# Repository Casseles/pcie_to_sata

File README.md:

# 4-Layer PCIe-to-SATA Adapter (Marvell 88SE9215).

*3D rendering top side (KiCad Raytracing)*

---

## 1. Project Overview
A compact 4-layer PCIe Gen2 x1 to 4-Port SATA 6 Gbps expansion card designed around the **Marvell 88SE9215** controller. 
This project serves as a first step into a homemade NAS server (to simply store data like pictures or videos). 
The goal was to make it from old hardware like a laptop, this card would help to add storage from HDD or SDD from the PCIe port.
I designed everything so it can be made with **JLCPCB SMT Assembly** but the price is too expensive for now to take it into manufacturing.

---

## 2. Key Specifications & System Architecture

| Feature | Specification |
| :--- | :--- |
| **Host Interface** | PCIe Gen2 x1 (5.0 Gbps per lane, Gold Finger PCB Edge Connector) |
| **SATA Controller** | Marvell 88SE9215 (76-pin QFN) |
| **SATA Ports** | 4x Standard 7-pin SATA 6 Gbps connectors |
| **Clocking** | 25.000 MHz Passive Crystal Resonator (SMD 3225 4-Pin, $C_L = 12\text{ pF}$) |
| **Power Supply** | PCIe +3.3V bus power to dual step-down buck regulators ($1.8\text{ V}$ & $1.0\text{ V}$) |
| **PCB Form Factor** | 4-Layer Stack-up, ENIG finish, Chamfered PCIe Edge |

### Block Diagram
```text
  ┌─────────────────┐       ┌───────────────────────┐       ┌──────────────┐
  │  PCIe Gen2 x1   │ ────> │   Marvell 88SE9215    │ ────> │  4x SATA III │
  │ Edge Connector  │       │       (QFN-76)        │       │  Connectors  │
  └─────────────────┘       └───────────────────────┘       └──────────────┘
           │                            ▲
           │                            │ 25 MHz
         +3.3V                  ┌───────────────┐
           ▼                    │ 25MHz Crystal │
   ┌───────────────┐            └───────────────┘
   │ DC-DC Bucks   │
   │ 1.8V & 1.0V   │
   └───────────────┘
```

## 3. Hardware Design & Signal Integrity

### Stack-up 

Designed for a 4-layer PCB stack-up :
- Layer 1 : High-speed differential pairs (PCIe & SATA) + buck regulator's components.
- Layer 2 : Ground plane.
- Layer 3 : Power planes (+3V3 / +1V8 / +1V0).
- Layer 4 : Decoupling capacitors, simple routing. 

### Power Distribution Network

- Dual Buck converter (MP2122) supplying power for core (+1V0) and I/O (+1V8).  
A switching regulator has been used and not an LDO because, to transform a +3V3 into a +1V0, and LDO would dissipate all additionnal voltage into heat, which could be dangerous.
- Low ESR ceramic decoupling capacitors placed on bottom layer to minimize loop inductance. 
To calculate inductances and resistances around the Buck converter, I followed the MP2122 datasheet.  

### Differential pair

To calculate width of the traces inside a differential pair, I used Saturn PCB Toolkit.  
Based on FR4 TG135 caracteristics (JLCPCB basic) and aiming for a 100 Ohms impedance for both SATA and PCIe differential pairs,  
I found a spacing between traces of 0,13mm and a width of 0,09mm.  
There are 3 differential pairs on PCIe : PRX, PTX and CLK.
For the first two, as the pins on the chip were inverted compared to the PCIe port, I switched them.  
The PCIe 2.0 specifications indicate a lane polarity that permits this kind of switch.  

## 4. Design for Manufacturing

- Fiducials placed on edge rails to ensure optical alignment as well as pick & place (SMT components).
- PCIe Edge connector designed with ENIG surface finish for high insertion durability.
- Components matched to JLCPCB SMT library.

## 5. Repository Structure

.  
├── docs/  
│  ├── schematic.pdf  
│  ├── pcb_layout.pdf  
│  └── images/  
├── hardware/  
└── manufacturing/  
   ├── gerbers/   
   ├── bom/  
   └── cpl/  

## 6. Verification & DRC status

- Schematic : ERC clean (0 errors)
- PCB Layout : DRC clean (0 errors)

## 7. Future improvements

The first step would be to manufacture this pcb and test it's accuracy.  
For a second version, it would be interesting to add power to SATA connectors as this version only deals with data and an additionnal power input is needed for all hard drivers.  
It would be wise to also rethink the architecture around the connectors so that they can be pluged directly to the board without an additionnal cable.

## 8. Licence

Distributed under the MIT License. See LICENSE for more information.

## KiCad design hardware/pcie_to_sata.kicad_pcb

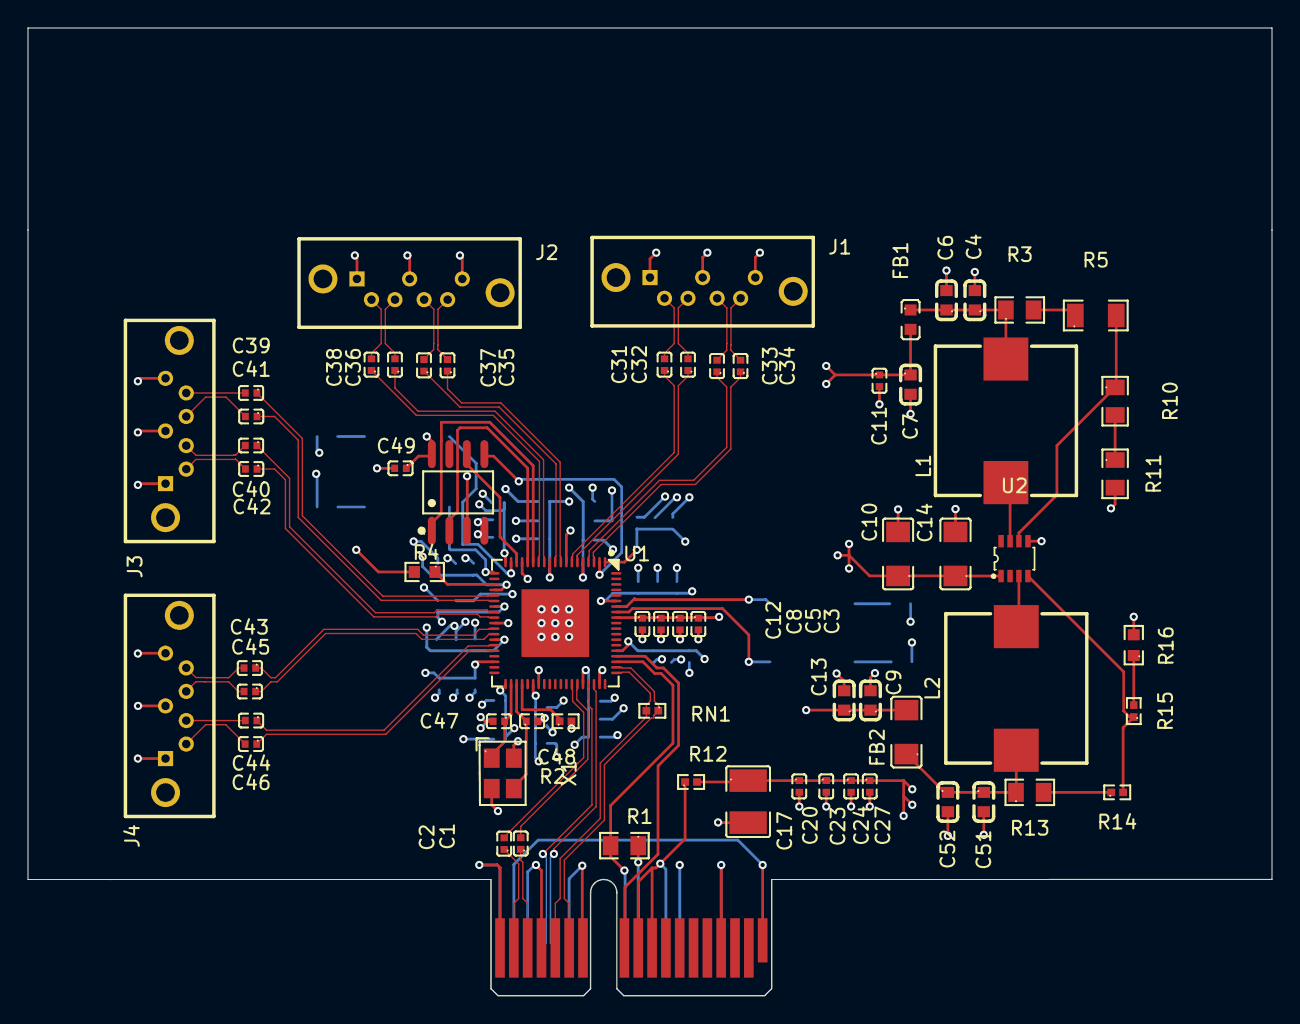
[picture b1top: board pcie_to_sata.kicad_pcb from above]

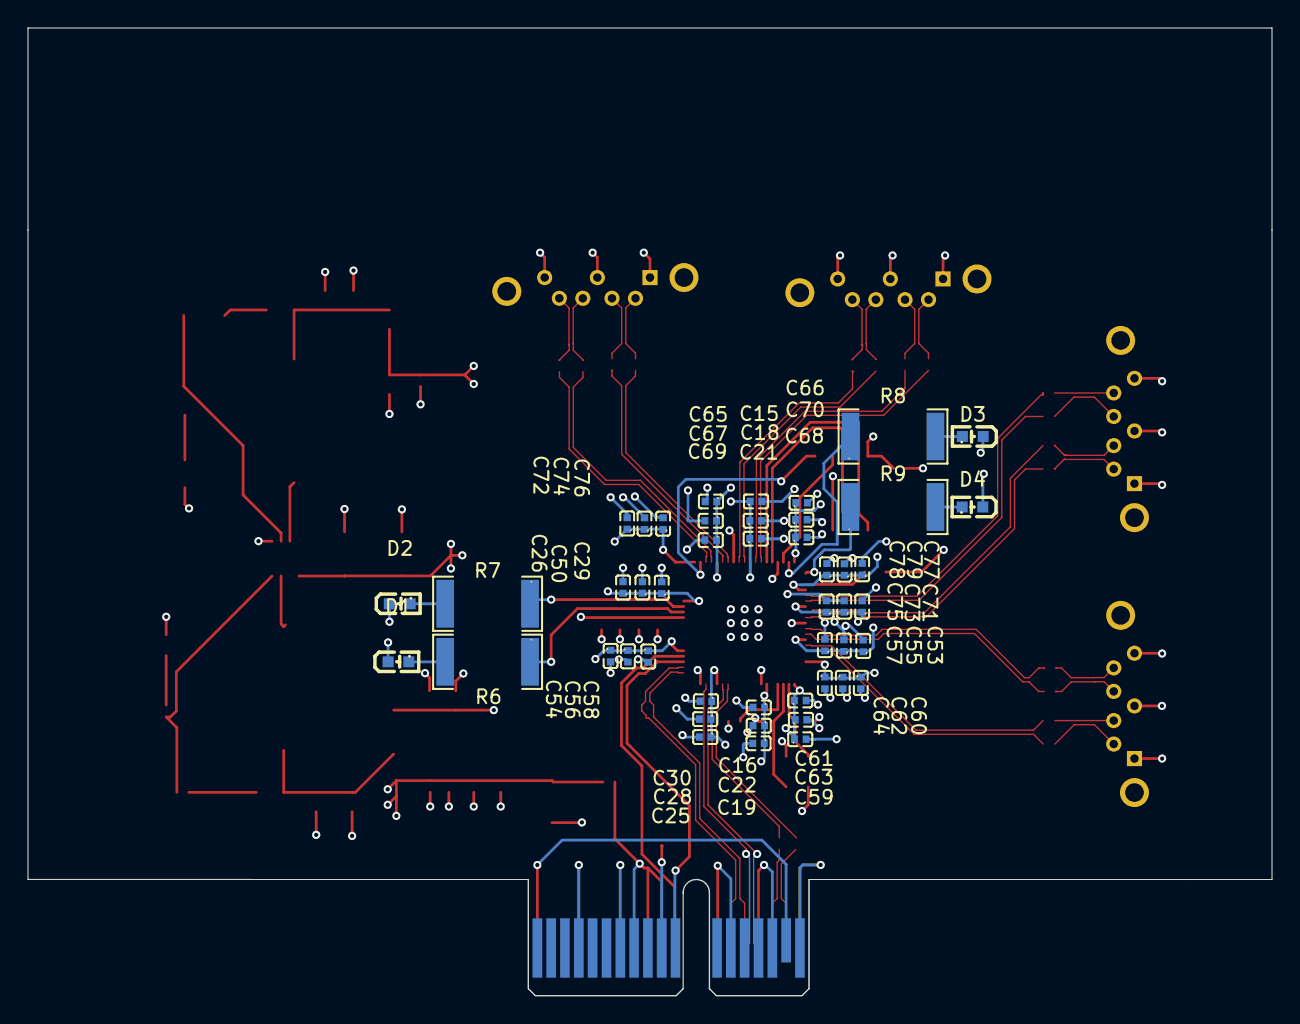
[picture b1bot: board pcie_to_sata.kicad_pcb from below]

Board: 4 copper layers, 90.0 x 70.0 mm, 113 parts (48 on the bottom side), 75 nets.

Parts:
C1, C2, C3, C5, C8, C11, C12, C15, C16, C20, C23, C24, C25, C26, C27, C49, C53, C54, C59, C60, C65, C66, C71, C72, C77: .1u; C0402
C4, C6, C51, C52: 10u; C0603
C7, C9: 2.2u; C0603
C10, C14: 22u; C1206
C13: 1u; C0603
C17: 100u; C1210
C18, C19, C22, C28, C29, C31, C32, C33, C34, C35, C36, C37, C38, C39, C40, C41, C42, C43, C44, C45, C46, C50, C55, C56, C58, C61, C62, C64, C67, C68, C70, C73, C74, C76, C78, C79: .01u; C0402
C21, C30, C57, C63, C69, C75: 1000p; C0402
C47, C48: 18p; C0402
D1, D2, D3, D4: LED; LED-SMD_L1.6-W0.8-R-RD
FB1: FerriteBead; L0603
FB2: FerriteBead; L1206
J1, J2, J3, J4: CONN-TH_SATA-501-M07S1BY-A
J5: Bus_PCI_Express_x1; BUS_PCIexpress_x1
L1, L2: 1.5u; IND-SMD_L10.8-W10.2_IHLP4040DZER1R8M11
R1: 4,7k; R0805
R2: 6.04k; R0402
R3: 750k; R0805
R4, R16: 10k; R0603
R5: 56k; R1206
R6, R7, R8, R9: 100; R2512
R10: 390k; R0805
R11: 22k; R0805
R12: 0; R0402
R13: 560k; R0805
R14: 39k; R0402
R15: 910k; R0402
RN1: 100; R0402
U1: QFN-76_L9.0-W9.0-P0.40-TL-EP4.9
U2: TSOT-23-8_L2.9-W1.6-P0.65-LS2.8-BL
U3: FM25Q08B-SO-T-G; SOP-8_L5.0-W4.0-P1.27-LS6.0-BL
X1: X322525MSB4SI; CRYSTAL-SMD_4P-L3.2-W2.5-BL-2

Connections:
+1V0: C9.1, C13.1, C16.1, C19.1, C22.1, C26.1, C29.1, C50.1, C54.1, C56.1, C58.1, C60.1, C62.1, C64.1, C66.1, C68.1, C70.1, C72.1, C74.1, C76.1, C77.1, C78.1, C79.1, FB2.2, U1.1 (VDD), U1.19 (VDD), U1.23 (VDD), U1.36 (VDD), U1.44 (VDD), U1.62 (VDD), U1.71 (VDD)
+1V0_unf: C51.1, C52.1, FB2.1, L2.2, R13.1
+1V8: C7.1, C11.1, C15.1, C18.1, C21.1, C25.1, C28.1, C30.1, C53.1, C55.1, C57.1, C59.1, C61.1, C63.1, C65.1, C67.1, C69.1, C71.1, C73.1, C75.1, FB1.2, U1.5 (VAA2_3), U1.11 (VAA2_2), U1.26 (VAA2_1), U1.32 (VAA2_0), U1.39 (VAA_1), U1.53 (AVDD0)
+1V8_unf: C4.1, C6.1, FB1.1, L1.1, R3.1
+3V3: C3.1, C5.1, C8.1, C10.1, C12.1, C14.1, C17.1, C20.1, C23.1, C24.1, C27.1, C49.1, D1.2 (A), D2.2 (A), D3.2 (A), D4.2 (A), R12.2, U1.16 (VDDIO), U1.68 (VDDIO), U2.1 (IN), U3.3 (WP#(DQ2)), U3.8 (VCC)
+3V3_unf: J5.A9 (+3.3V), J5.A10 (+3.3V), J5.B8 (+3.3V), R12.1
/pcie_to_sata/GPIO1: R6.1, U1.69 (GPIO1)
/pcie_to_sata/GPIO2: R7.1, U1.70 (GPIO2)
/pcie_to_sata/GPIO3: R8.1, U1.18 (GPIO3)
/pcie_to_sata/GPIO4: R9.1, U1.20 (GPIO4)
/pcie_to_sata/HSIN: C2.1, J5.A17 (PERn0)
/pcie_to_sata/HSIP: C1.1, J5.A16 (PERp0)
/pcie_to_sata/PCIE_AUX3: J5.B10 (3.3Vaux), R1.1
/pcie_to_sata/PCLKN: J5.A14 (REFCLK-), RN1.2, U1.58 (CLKP)
/pcie_to_sata/PCLKP: J5.A13 (REFCLK+), RN1.1, U1.59 (CLKN)
/pcie_to_sata/PERST_N: J5.A11 (~PERST), U1.61 (PERST_N)
/pcie_to_sata/PRX_0N: J5.B15 (PETn0), U1.54 (PRXN0)
/pcie_to_sata/PRX_0P: J5.B14 (PETp0), U1.55 (PRXP0)
/pcie_to_sata/PTX_0N: C1.2, U1.52 (PTXP0)
/pcie_to_sata/PTX_0P: C2.2, U1.51 (PTXN0)
/pcie_to_sata/SPI_CLK: U1.17 (SPI_CLK), U3.6 (CLK)
/pcie_to_sata/SPI_CS: U1.14 (SPI_CS), U3.1 (~CS)
/pcie_to_sata/SPI_DI: U1.15 (SPI_DI), U3.2 (DO(DQ1))
/pcie_to_sata/SPI_DO: U1.2 (SPI_DO), U3.5 (DI(DQ0))
/pcie_to_sata/S_RXN0: C33.1, U1.4 (RXN_3)
/pcie_to_sata/S_RXN0_: C33.2, J1.5
/pcie_to_sata/S_RXN1: C37.1, U1.10 (RXN_2)
/pcie_to_sata/S_RXN1_: C37.2, J2.5
/pcie_to_sata/S_RXN2: C41.1, U1.25 (RXN_1)
/pcie_to_sata/S_RXN2_: C41.2, J3.5
/pcie_to_sata/S_RXN3: C45.1, U1.31 (RXN_0)
/pcie_to_sata/S_RXN3_: C45.2, J4.5
/pcie_to_sata/S_RXP0: C34.1, U1.3 (RXP_3)
/pcie_to_sata/S_RXP0_: C34.2, J1.6
/pcie_to_sata/S_RXP1: C35.1, U1.9 (RXP_2)
/pcie_to_sata/S_RXP1_: C35.2, J2.6
/pcie_to_sata/S_RXP2: C39.1, U1.24 (RXP_1)
/pcie_to_sata/S_RXP2_: C39.2, J3.6
/pcie_to_sata/S_RXP3: C43.1, U1.30 (RXP_0)
/pcie_to_sata/S_RXP3_: C43.2, J4.6
/pcie_to_sata/S_TXN0: C32.1, U1.6 (TXN_3)
/pcie_to_sata/S_TXN0_: C32.2, J1.3
/pcie_to_sata/S_TXN1: C36.1, U1.12 (TXN_2)
/pcie_to_sata/S_TXN1_: C36.2, J2.3
/pcie_to_sata/S_TXN2: C40.1, U1.27 (TXN_1)
/pcie_to_sata/S_TXN2_: C40.2, J3.3
/pcie_to_sata/S_TXN3: C44.1, U1.33 (TXN_0)
/pcie_to_sata/S_TXN3_: C44.2, J4.3
/pcie_to_sata/S_TXP0: C31.1, U1.7 (TXP_3)
/pcie_to_sata/S_TXP0_: C31.2, J1.2
/pcie_to_sata/S_TXP1: C38.1, U1.13 (TXP_2)
/pcie_to_sata/S_TXP1_: C38.2, J2.2
/pcie_to_sata/S_TXP2: C42.1, U1.28 (TXP_1)
/pcie_to_sata/S_TXP2_: C42.2, J3.2
/pcie_to_sata/S_TXP3: C46.1, U1.34 (TXP_0)
/pcie_to_sata/S_TXP3_: C46.2, J4.2
/pcie_to_sata/TESTMODE: R4.1, U1.22 (TestMode)
/pcie_to_sata/WAKE_N: J5.B11 (~WAKE), R1.2, U1.60 (WAKE_N)
/pcie_to_sata/XTLI: C47.1, U1.40 (XTLIN_OSC), X1.1 (OSC1)
/pcie_to_sata/XTLOUT: C48.1, U1.41 (XTLOUT), X1.3 (OSC2)
GNDREF: C3.2, C4.2, C5.2, C6.2, C7.2, C8.2, C9.2, C10.2, C11.2, C12.2, C13.2, C14.2, C15.2, C16.2, C17.2, C18.2, C19.2, C20.2, C21.2, C22.2, C23.2, C24.2, C25.2, C26.2, C27.2, C28.2, C29.2, C30.2, C47.2, C48.2, C49.2, C50.2, C51.2, C52.2, C53.2, C54.2, C55.2, C56.2, C57.2, C58.2, C59.2, C60.2, C61.2, C62.2, C63.2, C64.2, C65.2, C66.2, C67.2, C68.2, C69.2, C70.2, C71.2, C72.2, C73.2, C74.2, C75.2, C76.2, C77.2, C78.2, C79.2, J1.1, J1.4, J1.7, J2.1, J2.4, J2.7, J3.1, J3.4, J3.7, J4.1, J4.4, J4.7, J5.A4 (GND), J5.A12 (GND), J5.A15 (GND), J5.A18 (GND), J5.B4 (GND), J5.B7 (GND), J5.B13 (GND), J5.B16 (GND), J5.B18 (GND), R2.2, R4.2, R11.2, R16.2, U1.8 (VSS), U1.29 (VSS), U1.45 (VSS), U1.56 (VSS), U1.77 (EPAD), U2.5 (GND), U3.4 (VSS), X1.2 (GND), X1.4 (GND)
unnamed: D1.1 (K), R6.2
unnamed: D2.1 (K), R7.2
unnamed: D3.1 (K), R8.2
unnamed: D4.1 (K), R9.2
unnamed: J5.A1 (~PRSNT1), J5.B17 (~PRSNT2)
unnamed: R3.2, R5.1
unnamed: R10.2, R11.1
unnamed: R13.2, R14.1
unnamed: R15.2, R16.1
unnamed: R2.1, U1.42 (ISET)
unnamed: R5.2, R10.1, U2.6 (FB1)
unnamed: R14.2, R15.1, U2.4 (FB2)
unnamed: L1.2, U2.7 (SW1)
unnamed: L2.1, U2.3 (SW2)

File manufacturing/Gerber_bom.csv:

Designator,Footprint,Quantity,Value,LCSC Part #
"C1, C11, C12, C15, C16, C2, C20, C23, C24, C25, C26, C27, C49, C5, C53, C59, C60, C65, C66, C71, C72",C0402,21,.1u,C85735
"C10, C14",C1206,2,22u,C1859
C13,C0603,1,1u,C1691
C17,C1210,1,100u,C90143
"C18, C19, C22, C28, C50, C55, C56, C62, C68",C0402,9,.01u,C85735
"C21, C57, C63, C69",C0402,4,1000p,C85735
"C29, C31, C32, C33, C34, C35, C36, C37, C38, C39, C40, C41, C42, C43, C44, C45, C46, C58, C61, C64, C67, C70, C73",C0402,23,.01u,C1523
"C3, C54, C77, C8",C0402,4,.1u,C1525
C30,C0402,1,1000p,C1523
"C4, C51, C52, C6",C0603,4,10u,C1691
"C47, C48",C0402,2,18p,C1523
"C7, C9",C0603,2,2.2u,C1691
"C74, C76, C78, C79",C0402,4,.01u,C1525
C75,C0402,1,1000p,C1525
"D1, D2, D3, D4",LED-SMD_L1.6-W0.8-R-RD,4,LED,C2286
FB1,L0603,1,FerriteBead,C963848
FB2,L1206,1,FerriteBead,C16902
"J1, J2, J3, J4",CONN-TH_SATA-501-M07S1BY-A,4,~,C7500838
J5,BUS_PCIexpress_x1,1,Bus_PCI_Express_x1,
"L1, L2",IND-SMD_L10.8-W10.2_IHLP4040DZER1R8M11,2,1.5u,C845071
R1,R0805,1,"4,7k",C1404
R10,R0805,1,390k,C1404
R11,R0805,1,22k,C17560
R12,R0402,1,0,C17168
R13,R0805,1,560k,C1404
R14,R0402,1,39k,C25076
R15,R0402,1,910k,C11866
"R16, R4",R0603,2,10k,C15401
R2,R0402,1,6.04k,C25913
R3,R0805,1,750k,C1404
R5,R1206,1,56k,C4513
"R6, R7, R8, R9",R2512,4,100,C15262
RN1,R0402,1,100,C425365
U1,QFN-76_L9.0-W9.0-P0.40-TL-EP4.9,1,~,C713244
U2,TSOT-23-8_L2.9-W1.6-P0.65-LS2.8-BL,1,~,C3194324
U3,SOP-8_L5.0-W4.0-P1.27-LS6.0-BL,1,FM25Q08B-SO-T-G,C696825
X1,CRYSTAL-SMD_4P-L3.2-W2.5-BL-2,1,X322525MSB4SI,C13740
